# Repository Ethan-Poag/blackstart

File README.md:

# Project Blackstart

Open-source diesel generator controller: STM32 safety MCU, Raspberry Pi CM5 for UI and connectivity,
dual ADE9000 metering (600 V class), 12.1" display, 12 backlit keys, external LTE router over Ethernet.

Status: schematic complete (ERC 0/0), layout and enclosure in progress. Prototype for the maintainer's own use first.

**Board status on the m7 branches (m7-wip):** gate checkpoint only — 789 KiCad-unconnected items (was 791), NOT fab-ready, NOT safety-reviewed, NOT certified (600 V sign-off by a qualified safety engineer outstanding).
Not certified. Do not rely on it for safety until independently tested and reviewed.

See DESIGN_NOTES.md, docs/, and LICENSING.md.

## +12V rail notes (m7-wip, 2026-10-26)
- The 470 uF bulk caps C17/C18 (CP_Elec_10x10.5) on +12V sit about 160 mm (C17) and 174 mm (C18) from the LM5176 output FET Q6. The builder may want to move them near Q6. No ceramic bulk sits at Q6: the nearest +12V caps are C96 100 nF (11.6 mm) and C14 1 uF (24.6 mm).
- Trunk limit (inferred, IPC-2221 10 C, 1 oz outer assumed): narrowest trunk segment 1.5 mm, about 3.2 A supported against roughly 3.7 A estimated for U3+U15.
- Still unpowered on +12V: U24.3/C125 (backlight boost), U2.24 (LM5176 BIAS), C17, C18.

**Fusing:** Genctl has no on-board fuses (PTCs on small signal outputs only). The DI bias terminals (J21.6, J22.1) are for the digital-input contacts only: no external loads. The power-box K3 glow contactor (ALEV100-B/-C) has polarised load terminals: observe +A1 / -A2 (see docs/INSTALL_SAFETY.md). Do not plug or unplug the 600 V sense plugs J7/J8 (J28/J29) live: isolate the source or open the metering fuses first. Their field wire must be 600 V rated and stripped to 10 mm (Phoenix 1777859 plug), with no bare copper past the plug body; the LEFT_HV enclosure window needs its tool-removable-only hood (docs/INSTALL_SAFETY.md). All fuses and the power relays sit in the separate power box (docs/INSTALL_SAFETY.md, review/bom_final/BOM_powerbox.csv). Every output (FUEL, CRANK, GLOW, GCB/MCB,
AUX1–10, ESTOP_TRIP) has its own power box fuse position ahead of the relay or
solenoid, no larger than the output's maximum (5 A standard blade for FUEL/CRANK, which are limited to 2.8 A; 2 A small outputs; 2 A
ESTOP_TRIP relay drive) and sized down to the real load. The 30 A battery fuse does not protect individual
outputs. The J23.1/2 E-stop/fuel feed has its own 10 A ATO/ATC fuse (>=58 V DC, >=16 AWG wire) at power box position F2, after the 30 A battery fuse; that feed is not behind the over-voltage cut-off and must stay within the declared supply range (9–32 V continuous, up to 36 V for at most 60 s), never above about 40 V. Hardware maximum per main output: interposing relay coil class <= 2.8 A (software trip 3.0 A); E-stop trip coil < 1.70 A (U68, R407 47k; bench-measure); where a circuit has a lower limit or a 2 A fuse, that lower limit governs. Fit a flyback diode across every external coil. Declared limit: 12 V and 24 V DC battery systems only, with the battery permanently connected as the buffer. Supply 9–32 V DC continuous; up to 36 V for at most 60 s (24 V jump-start), during which the controller may switch itself off; above its over-voltage trip point, 36.35-40.06 V (component tolerance), it disconnects its internal supply, and after such an over-voltage trip the supply must fall below about 33 V before the controller restarts by itself. Short ISO 7637-type pulses are tolerated. Load dump of any kind, including a centrally suppressed 58 V load dump (ISO 16750-2 Test B), is not supported and has not been tested. The fuel solenoid must be energize-to-run. See docs/INSTALL_SAFETY.md. Not certified.

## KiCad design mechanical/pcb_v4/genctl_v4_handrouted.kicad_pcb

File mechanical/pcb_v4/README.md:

# Blackstart PCB v4: connectivity-driven placement and route pipeline

> **SUPERSEDED (N4, m7-sch 3c, 2026-10-28):** the schematic has no on-board fuse; battery net BAT_IN; installer fits an external fuse <=10 A standard (non-time-delay), >=58 V DC in the battery lead. Every F1 / VBAT_F / "fuse F1 10 A" / "10 A ATO" mention in this file describes the as-built .kicad_pcb (which still carries F1 clips and net VBAT_F until the board update) and is historical; the VBAT_F copper becomes BAT_IN when the board is updated. The 10 A copper figures remain a copper-capacity record only.

The board opens in KiCad 9/10 with `genctl_v4_routed.kicad_pcb` and `genctl_v4.kicad_pro`. The footprints are embedded and no plugins are needed.

## Pipeline (`pipeline.sh`)
Run it on the build box with KiCad 9 pcbnew python, Freerouting 2.5 and Java 25.

1. **place** (`place_v4.py`): hard constraints are locked first:
   - edges, keys, CM5 and display connectors
   - the 600 V box with its 13 mm barrier and slots, plus the isolators straddling it
   - posts, holes and the strap corridor

   After that come the **functional seeds**:
   - STM32, DSI83, bucks and ideal diode
   - ADE9000s, the CT stack and MOVs
   - J10/J11, which are rear-facing

   Every other IC goes to the weighted centroid of the parts it is already connected to (greedy, most-connected first). Each R/C/D/FB is assigned to its nearest IC on the same schematic sheet and lands right at the IC pin it shares, so decaps sit tight to their pins. Hot parts are confined to the HV box. Parts touching the line nets keep ≥1.4 mm between each other.
2. **critical** (`route_v4.py setup`):
   - **Netclasses:**
     - PWR 0.5 mm
     - DIFF100 0.11/0.15 (Ethernet, LVDS, DSI)
     - DIFF90 0.15/0.18 (USB)
     - HV_LINE 1.5 mm clearance (IPC-2221B B2, 600 V, inside the HV box)
   - **Plane zones:**
     - LV area: GND on In1/In4, +3V3_SAFE on In3
     - HV box: GND_AC on In1/In4, +3V3_AC on In3
   - **Plane fan-out:** a short stub and via from every SMD pad on a plane net, plus a via-in-pad grid on exposed pads.
3. **autoroute**: the remaining nets go to Freerouting via DSN/SES (`--router.fanout.enabled=false`).
4. **DRC**: `kicad-cli pcb drc`.
5. **render**: `render_v4.py`.

Rules: 0.10 mm track/space minimum, 0.20/0.40 mm vias. The impedance widths are **estimates** for JLC06161H-3313 and must be checked in JLC's impedance calculator.

**Fab note (m7-wip, 2026-10-25):** two DSI83_REFCLK vias, at (161.5, 126.7) and (162.0, 125.65) mm, are **0.15 mm drill / 0.30 mm pad**. Every other via is ≥0.2/0.35. I tried enlarging them to 0.2/0.35, but they do not fit: that breaks the DIFF100 clearance (0.125 vs 0.15 mm), the hole clearance (0.18 vs 0.20 mm) and the zone clearance (0.176 vs 0.20 mm). The board therefore needs JLC's "smaller via" option (0.15/0.25–0.3 mm class) at order time, which may add cost; check the JLC quote. The project's minimums are min through-hole 0.15 mm and min via 0.30 mm. The working and repo .kicad_pro files now agree on these values.

**Builder note (m7-wip, 2026-10-25): RV3 is NOT wired.** The GEN-side MOV RV3, at (25.26, 154.08) mm on B.Cu, is placed, but its pads RV3.1 (GEN_L3) and RV3.2 (GEN_N) have no copper. There is no legal 600 V path to its spot in the BUS area; it is an accepted placement exception (see HV_ACCEPTED_DEVIATIONS.md item 3). Do not assume GEN-side L3–N surge protection from RV3 on this board revision, and do not bodge-wire it without an HV spacing check.

## Known limit (m7-wip, 2026-10-26)
Superseded (2026-10-27, S3c/c6b): the board battery path is a 10 A path (F1 10 A) at 18 °F (10 °C) rise, INFERRED from the measured copper with 1 oz outer ASSUMED, not certified: VBAT_P Q2→Q3 F 8.76 / B 4.54 mm (11.5 / 7.2 A; F+B 18.7 A per the reviewer's tight-pad neck method, review/s3c6c/review.md, same on base and c6c; the earlier B 5.22 mm / 7.9 A / F+B 19.5 A was a method artefact, B alone < 10 A, so F+B sharing through the VBAT_P transfer vias is required: VBAT_P vias at the Q2 / Q3 ends, MEASURED with review/s3c6b/via_count.py (all 0.3/0.6 mm vias): primary method via-edge-to-pad-edge (any part of the via pad within r of any edge of the FET pads used: Q2 pads 1-3, Q3 pad 5) 25 / 25 within 5 mm and 40 / 35 within 8 mm; reviewer method via-centre-to-point (via centre within r of Q2 point (254.6, 151.0) / Q3 point (228.02, 140.07)) 17 / 14 within 5 mm and 34 / 25 within 8 mm; identical at 950b8a1 and S3c/c6c; 14 is met at both ends within 5 mm, exactly at the Q3 end), VBAT_DD Q1→Q2 F 7.54 / B 7.51 mm (10.3 / 10.3 A; F+B 20.7 A), VBAT_F F1→Q1 B 8.02 mm (10.8 A, reviewer tight-pad method; B only at Q1; F 8.95 mm before c6c, 1.92 mm after c6c, not counted) [M widths, tneck erosion on gate/s3c6b; amps I by IPC-2221 outer k 0.048 at 18 °F (10 °C) rise, 1 oz ASSUMED]. Caveat: the 10 A figure is the copper only. Continuous load is also limited by F1: a 10 A ATO carries at most about 8 A at 149 °F (65 °C) ambient (Littelfuse 287 ATOF derating, final_power_spec.md §1; datasheet pages UNVERIFIED). The battery wiring and the mating connector must be rated for the load as well. See docs/ROUTING_PLAN.md §8. Load shedding is fault-only, not a normal-operation behavior.

s3c6h (2026-10-27): C297 (220 nF / 100 V X7R since s3c6i; first 100 nF) on VBAT_F is the LM74800 CIN (TI SNOSD95C p23), at F.Cu (249.6, 137.0). The C1.1 VBAT_DD link moved from PWR to GND2, so the VBAT_F PWR pour is whole again: VBAT_F F1→Q1 PWR neck 8.952 mm [M], B 8.021 mm unchanged. See docs/ROUTING_PLAN.md §8.3. Not certified.

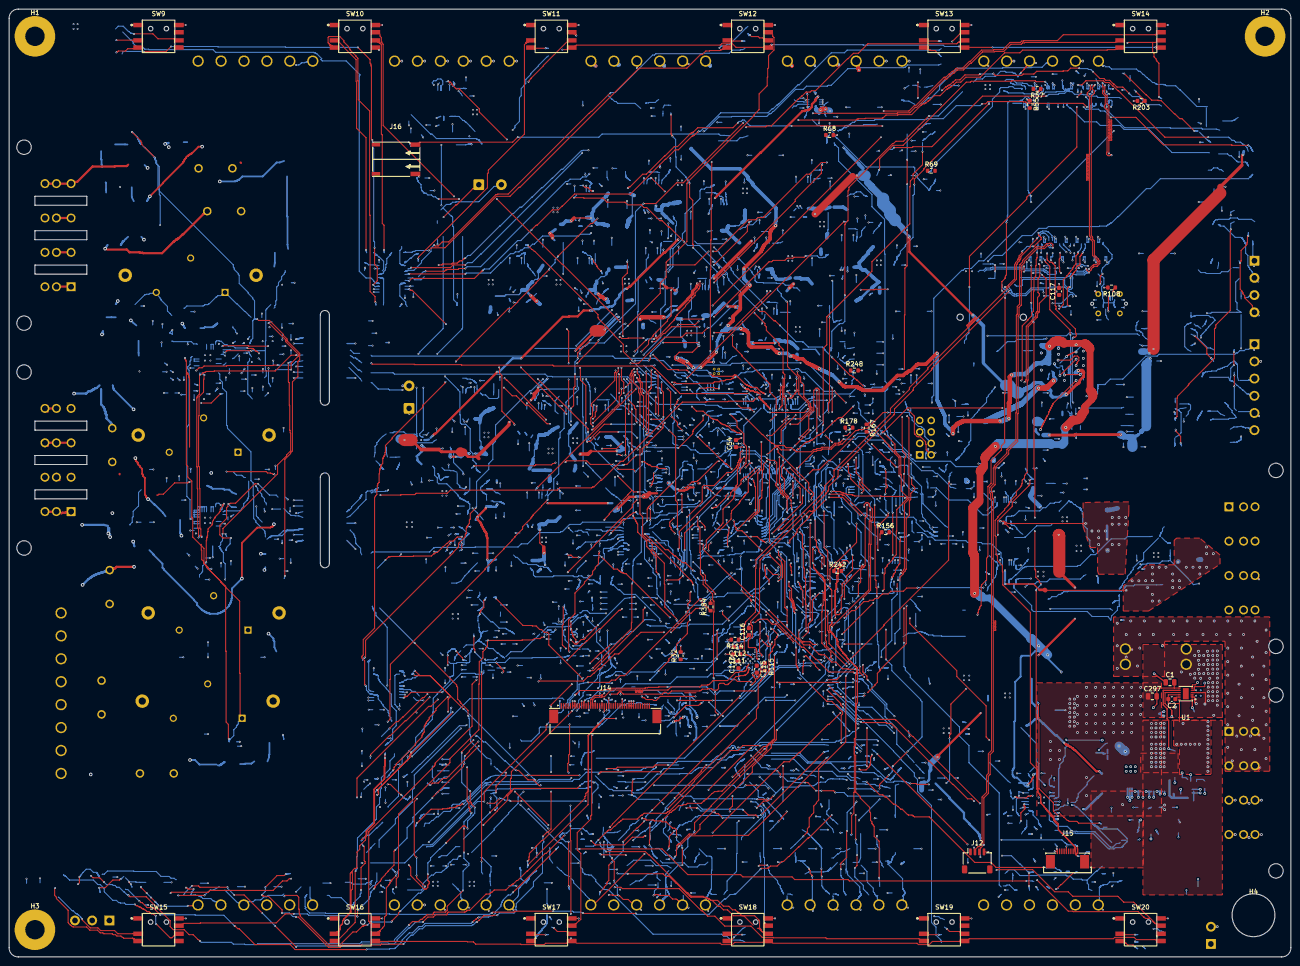
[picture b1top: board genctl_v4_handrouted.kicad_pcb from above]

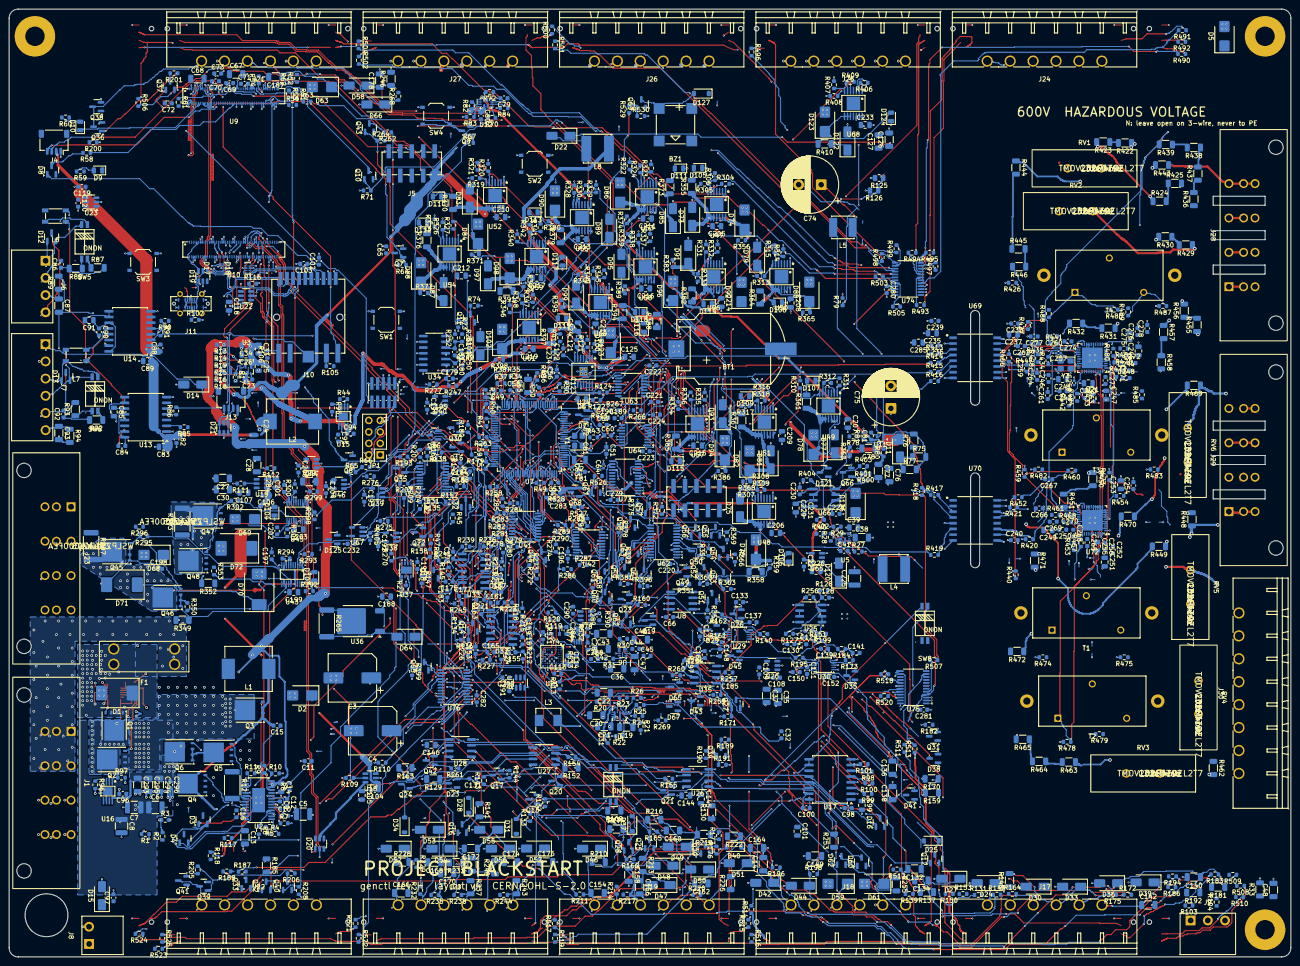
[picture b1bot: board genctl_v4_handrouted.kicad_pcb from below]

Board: 6 copper layers, 284.0 x 210.0 mm, 1184 parts (1138 on the bottom side), 819 nets.

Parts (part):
BT1: CR2032; BS-CR2032-8
BZ1: MLT-8530; MLT-8530_buzzer
C1, C39, C144, C145, C146, C188, C199, C203, C205, C206, C207, C208, C209, C210, C211, C212, C213, C214, C215, C216, C217, C218, C219, C233: 100n; C_0805_2012Metric
C2, C15, C16, C23, C31, C40, C49, C50, C51, C52, C53, C54, C57, C60, C65, C66, C69, C70, C71, C73, C79, C82, C84, C88, C90, C94, C96, C98, C100, C102, C110, C111, C112, C113, C128, C130, C131, C133, C135, C137, C139, C141, C143, C148, C150, C151, C152, C153, C155, C157, C159, C161, C163, C165, C167, C169, C171, C173, C175, C177, C179, C180, C182, C183, C184, C186, C189, C190, C191, C192, C193, C194, C195, C196, C200, C204, C220, C221, C223, C227, C228, C230, C231, C232, C234, C236, C238, C239, C240, C242, C244, C246, C248, C250, C252, C254, C256, C279, C280, C281, C282, C286, C288, C289, C290, C291, C292, C296: 100n; C_0603_1608Metric
C3, C4: 100u 50V; CP_Elec_10x10.5
C5, C6, C7, C8, C225: 10u; C_1210_3225Metric
C9, C12: 220p; C_0603_1608Metric
C10, C122: 47n; C_0603_1608Metric
C11, C259, C260, C261, C262, C263, C264, C265, C266, C267, C268, C269, C270, C271, C272, C273, C274, C275, C276, C277, C278: 33n; C_0603_1608Metric
C13, C55, C126, C127: 4.7u; C_1206_3216Metric
C14: 1u; C_0805_2012Metric
C19, C20, C21, C22, C27, C28, C29, C30, C35, C36, C37, C46, C47, C67, C68, C76, C77, C78, C293, C294, C295: 22u; C_1206_3216Metric
C24, C32, C287: 100p; C_0603_1608Metric
C25, C26, C33, C34, C83, C85, C89, C91, C99, C101, C105, C107, C114, C118, C124, C125, C235, C237, C247, C255, C284, C285: 10u; C_0805_2012Metric
C38: 2.2u; C_1206_3216Metric
C41, C44, C45, C56, C72, C80, C81, C104, C106, C108, C109, C115, C120, C121, C129, C283: 1u; C_0603_1608Metric
C42, C43: 47u; C_1206_3216Metric
C48, C87, C93: 4.7n; C_1206_3216Metric
C58, C59: 2.2u; C_0603_1608Metric
C61, C62, C63, C64: 18p; C_0402_1005Metric
C74, C75: 20F 3.0V; CP_Radial_D12.5mm_P5.00mm
C86, C92: 4.7n; C_0603_1608Metric
C95, C97, C103, C116, C181, C222, C224: 10n; C_0603_1608Metric
C117, C119, C185: 1n; C_0603_1608Metric
C123, C198, C202: 470n; C_0603_1608Metric
C132, C134, C136, C138, C140, C142, C147, C149, C154, C156, C158, C160, C162, C164, C166, C168, C170, C172, C174, C176, C178, C187: 100n; C_1206_3216Metric
C197, C201: 68n; C_0603_1608Metric
C226, C229: 2.2u; C_0805_2012Metric
C241, C243, C245, C249, C251, C253: 4.7u; C_0805_2012Metric
C257, C258: 22p; C_0402_1005Metric
C297: 220n; C_0805_2012Metric
D1: SMDJ36CA; D_SMC
D2, D68, D69, D74, D76, D78, D80, D82, D84, D86, D88, D90, D92, D94, D96, D98, D100, D102, D123, D126: SMBJ33CA; D_SMB
D3, D4: BAS70; SOT-23
D5: SMBJ5.0A; D_SMB
D6, D9, D103, D104, D105, D106, D107, D108, D109, D110, D111, D112, D113, D114, D115, D116, D117, D118, D119: green; LED_0805_2012Metric
D7, D8, D121: BAT54C; SOT-23
D10, D124: red; LED_0805_2012Metric
D11: SS34; D_SMA
D12, D13: NUP2105L; SOT-23
D14, D15, D64, D73, D75, D77, D79, D81, D83, D85, D87, D89, D91, D93, D95, D97, D99, D101, D120, D122: SS110; D_SMA
D16: SM712; SOT-23
D17, D18: RClamp0524P; RClamp0524P_SLP2510P8
D19, D20, D21: USBLC6-2SC6; SOT-23-6
D22: SS36; D_SMA
D23: LM4040A25; SOT-23
D24, D27, D30, D33, D36, D39, D42, D44, D46, D47, D48, D49, D50, D51, D52, D53, D54, D55, D56, D57, D58, D66: SMAJ36CA; D_SMA
D25, D28, D31, D34, D37, D40, D127: 1N4148W; D_SOD-123
D26, D29, D32, D35, D38, D41, D43, D45, D60, D62: BAV99; SOT-23
D59, D61: SMBJ58CA; D_SMB
D63: SMBJ36CA; D_SMB
D65, D67, D125: BAT54S; SOT-23
D70, D72: SK1010C; D_SMC
D71: SMDJ24A; D_SMC
F1: 10A ATO (3557-2 clips); Keystone_3557-2_ATO_clips
FB1: 600R@100MHz; L_0603_1608Metric
H1, H2, H3: M4 bezel boss; MountingHole_4.3mm_M4_Pad
H4: PE boss clearance D9.5 NPTH; MountingHole_4.3mm_M4
J1: PC 5/4-GF-7,62 (battery in); PhoenixContact_PC5_4-GF-7.62_1720819
J2: SWD; FTSH-105-01_SWD
J3: Header B (MCU spare); PZ254-2-05-S_2x05_SMD
J4: Fan header (SM04B); JST_SH_SM04B-SRSS-TB_1x04-1MP_P1.00mm_Horizontal
J5: Header A (CM5 I2C/SPI); PZ254-2-05-S_2x05_SMD
J6: CAN1 (PC 5/4); WJ15EDGRC-3.81-4P
J7: Expansion bus (PC 5/6); WJ15EDGRC-3.81-6P
J8: Router 12V (3.81/2); WJ15EDGRC-3.81-2P
J9: RS-485 (PC 5/3); WJ15EDGRC-3.81-3P
J10: HR963380AE; HR963380AE_RJ45
J11: USB-C service; USB_C_Receptacle_HRO_TYPE-C-31-D-06B_Vertical
J12: Internal USB0 touch (SM04B); JST_SH_SM04B-SRSS-TB_1x04-1MP_P1.00mm_Horizontal
J13: Internal USB1 spare (SM04B); JST_SH_SM04B-SRSS-TB_1x04-1MP_P1.00mm_Horizontal
J14: LVDS FPC 40p 0.5mm; FPC_40P_0.5_05A20L40P
J15: Touch FPC 10p 0.5mm; FPC_10P_0.5_05B20L10P
J16: Backlight (JST SM02B-BHSS); SM02B-BHSS-1-TB
J17: J1A analog in (PC 5/6); KF2EDGRM-5.08-6P
J18: J1B COM/MPU (PC 5/6); KF2EDGRM-5.08-6P
J19: J2A DI1-6; KF2EDGRM-5.08-6P
J20: J2B DI7-12; KF2EDGRM-5.08-6P
J21: J3A E-stop/D+/VBAT/bias; KF2EDGRM-5.08-6P
J22: J3B; KF2EDGRM-5.08-6P
J23: J4 E-stop/fuel/crank (PC 5/4-7.62); PhoenixContact_PC5_4-GF-7.62_1720819
J24: J5A outputs; KF2EDGRM-5.08-6P
J25: J5B returns; KF2EDGRM-5.08-6P
J26: J6A AUX1-6; KF2EDGRM-5.08-6P
J27: J6B AUX7-10 + returns; KF2EDGRM-5.08-6P
J28: J7 GEN voltage (L1 L2 L3 N); PhoenixContact_PC5_4-GF-7.62_1720819
J29: J8 BUS voltage (L1 L2 L3 N); PhoenixContact_PC5_4-GF-7.62_1720819
J30: J9 CT secondaries (5A); KF2EDGRM-5.08-8P
JP1: JP1 CM5->MCU SWD (opt); PinHeader_2x04_P2.54mm_Vertical
L1: 4.7u; L_SPM10065
L2: 3.3u; L_MWSA1004S
L3: 2.2u; L_MWSA0503S
L4: 33u; L_SWPA6045S
L5: 1u; L_FNR5020S
L6, L7: ACT45B-510-2P; ACT45B_CMC
L8: 10u; L_SWPA6045S
Q1, Q2, Q3, Q4, Q5, Q6, Q45, Q46, Q47, Q48: BSC070N10NS5; TDSON-8-1
Q7, Q8, Q9, Q10, Q11, Q14, Q18, Q22, Q26, Q30, Q34, Q37, Q40, Q43, Q44, Q49, Q50, Q51, Q52, Q53, Q54, Q55, Q56, Q57, Q58, Q59, Q60, Q61, Q62, Q63, Q64, Q65, Q66, Q67, Q69: MMBT3904; SOT-23
Q12, Q16, Q20, Q24, Q28, Q32: MMBT3906; SOT-23
Q13, Q17, Q21, Q25, Q29, Q33: BSS84; SOT-23
Q15, Q19, Q23, Q27, Q31, Q35, Q38, Q41: DMN6075S; SOT-23
Q36, Q39, Q42: SI2309CDS; SOT-23
Q68: AO3401A; SOT-23
R1: 210k; R_0603_1608Metric
R2: 49.9k; R_0603_1608Metric
R3: 9.76k; R_0603_1608Metric
R4, R11, R19, R26, R28, R32, R43, R64, R66, R68, R71, R73, R81, R97, R110, R112, R114, R115, R116, R121, R133, R134, R136, R138, R139, R144, R145, R147, R149, R150, R155, R156, R158, R160, R161, R166, R167, R169, R171, R172, R177, R178, R180, R182, R183, R188, R189, R191, R193, R194, R196, R198, R200, R201, R203, R204, R205, R206, R208, R209, R261, R262, R264, R266, R268, R273, R275, R276, R277, R278, R279, R280, R281, R282, R283, R284, R285, R286, R287, R288, R289, R290, R291, R292, R298, R350, R353, R356, R359, R362, R365, R368, R371, R374, R377, R380, R383, R386, R389, R392, R395, R398, R403, R405, R406, R411, R527, R530: 100k; R_0603_1608Metric
R5, R212, R215, R218, R221, R224, R227, R230, R233, R236, R239, R242, R245, R248, R250, R252: 33k; R_0603_1608Metric
R6: 93.1k; R_0603_1608Metric
R7: 27.4k; R_0603_1608Metric
R8: 4.7k; R_0603_1608Metric
R9: 140k; R_0603_1608Metric
R10, R17, R24, R31, R42, R44, R45, R48, R49, R63, R65, R67, R69, R70, R72, R74, R78, R79, R83, R101, R113, R117, R118, R124, R127, R128, R132, R135, R143, R146, R154, R157, R165, R168, R176, R179, R187, R190, R202, R207, R257, R263, R267, R269, R270, R271, R272, R274, R351, R354, R357, R360, R363, R366, R369, R372, R375, R378, R381, R384, R387, R390, R393, R396, R399, R401, R402, R412, R420, R421, R528: 10k; R_0603_1608Metric
R12: 8m; R_2512_6332Metric
R13, R20: 121k; R_0603_1608Metric
R14, R21: 16k; R_0603_1608Metric
R15, R22, R296, R302: 0R; R_0603_1608Metric
R16: 75k; R_0603_1608Metric
R18, R25: 20k; R_0603_1608Metric
R23: 45.3k; R_0603_1608Metric
R27, R109, R111, R304, R307, R310, R313, R316, R319, R322, R325, R328, R331, R334, R337, R340, R343, R346: 40.2k; R_0603_1608Metric
R29: 43.2k; R_0603_1608Metric
R30: 18.7k; R_0603_1608Metric
R33, R89, R94, R422, R423, R424, R425, R429, R430, R431, R432, R436, R437, R438, R439, R443, R444, R445, R446, R448, R449, R450, R451, R455, R456, R457, R458, R462, R463, R464, R465, R469, R470, R471, R472: 1M; R_1206_3216Metric
R34, R35, R36, R37, R38, R39, R40, R41, R50, R51, R52, R53, R54, R55, R56, R57, R58, R59, R60, R61, R62, R85, R86, R90, R91, R96, R98, R99, R100, R131, R142, R153, R164, R175, R186, R306, R309, R312, R315, R318, R321, R324, R327, R330, R333, R336, R339, R342, R345, R348, R409, R413, R414, R415, R416, R417, R418, R419, R426, R427, R428, R433, R434, R435, R440, R441, R442, R447, R452, R453, R454, R459, R460, R461, R466, R467, R468, R473, R476, R477, R480, R481, R484, R485, R488, R489, R526, R529: 1k; R_0603_1608Metric
R46, R47, R119, R120, R259, R260: 2.2k; R_0603_1608Metric
R75, R76, R77: 150R; R_1206_3216Metric
R80: 715k; R_0603_1608Metric
R82: 33.2k; R_0603_1608Metric
R84: 29.4k; R_0603_1608Metric
R87, R88, R92, R93: 62R; R_1206_3216Metric
R95: 1.33k; R_0603_1608Metric
R102: 120R; R_1206_3216Metric
R103, R104: 680R; R_0603_1608Metric
R105, R106, R492, R495, R498, R501, R504, R507, R510, R513, R516, R519, R522, R525: 330R; R_0603_1608Metric
R107, R108: 5.1k; R_0603_1608Metric
R122: 180k; R_0603_1608Metric
R123: 232k; R_0603_1608Metric
R125, R126: 1.1R; R_0805_2012Metric
R129, R253, R255, R349, R352, R355, R358, R361, R364, R367, R370, R373, R376, R379, R382, R385, R388, R391, R394, R397, R410: 10k; R_1206_3216Metric
R130, R141, R152, R163, R174, R185: 2.49k; R_1206_3216Metric
R137, R148, R159, R170, R181, R192: 100R; R_1206_3216Metric
R140, R151, R162, R173, R184, R195, R197, R199: 18k; R_0603_1608Metric
R210, R213, R216, R219, R222, R225, R228, R231, R234, R237, R240, R243, R246: 4.7k; R_1206_3216Metric
R211, R214, R217, R220, R223, R226, R229, R232, R235, R238, R241, R244, R247, R249, R251: 68k; R_0603_1608Metric
R254, R256, R258: 1M; R_0603_1608Metric
R265: 10R; R_2512_6332Metric
R293, R299: 27k; R_0603_1608Metric
R294, R300: 35.7k; R_0603_1608Metric
R295, R301: 10R; R_0603_1608Metric
R297, R303: 1m; R_2512_6332Metric
R305, R308, R311, R314, R317, R320, R323, R326, R329, R332, R335, R338, R341, R344, R347, R408: 1.1k; R_0603_1608Metric
R400, R407, R533: 47k; R_0603_1608Metric
R404, R532: 200k; R_0603_1608Metric
R474, R475, R478, R479, R482, R483, R486, R487: 24.9R; R_0603_1608Metric
R490, R491, R493, R494, R496, R497, R499, R500, R502, R503, R505, R506, R508, R509, R511, R512, R514, R515, R517, R518, R520, R521, R523, R524: 470R; R_0603_1608Metric
R531: 22R; R_0603_1608Metric
RV1, RV2, RV3, RV4, RV5, RV6: TMOV20RP460E; TMOV20RP_P7.5mm_inline
SW1: RESET; SW_Push_1P1T_XKB_TS-1187A
SW2: BOOT0; SW_Push_1P1T_XKB_TS-1187A
SW3: nRPIBOOT; SW_Push_1P1T_XKB_TS-1187A
SW4: CM5 PWR; SW_Push_1P1T_XKB_TS-1187A
SW5, SW6: TERM; DSHP02TSGER_DIP2
SW7: TERM/BIAS; DSHP02TSGER_DIP2
SW8: BIAS; DSHP02TSGER_DIP2
SW9: BTN1; CTS_228E_RGB
SW10: BTN2; CTS_228E_RGB
SW11: BTN3; CTS_228E_RGB
SW12: BTN4; CTS_228E_RGB
SW13: BTN5; CTS_228E_RGB
SW14: BTN6; CTS_228E_RGB
SW15: BTN7; CTS_228E_RGB
SW16: BTN8; CTS_228E_RGB
SW17: BTN9; CTS_228E_RGB
SW18: BTN10; CTS_228E_RGB
SW19: BTN11; CTS_228E_RGB
SW20: BTN12; CTS_228E_RGB
T1, T2, T3, T4: AC1005; AC1005_CT
U1: LM74800QDRRRQ1; LM74800_WSON-12_3x3
U2: LM5176PWPR; HTSSOP-28-1EP_4.4x9.7mm_P0.65mm_EP2.85x5.4mm
U3, U4: TPS56637RPAR; TPS56637_VQFN-HR-10_RPA
U5: LMR36506RRPER; LMR36506_VQFN-HR-9_RPE
U6: TPS2116DRLR; SOT-583-8
U7: STM32H743VIT6; LQFP-100_14x14mm_P0.5mm
U8: FM24CL64B; SOIC-8_3.9x4.9mm_P1.27mm
U9: CM5 (conn A); DF40C-100DS-0.4V
U10: CM5 (conn B); DF40C-100DS-0.4V_B
U11: TPS61023DRLR; SOT-563
U12: TPS2121RUXR; TPS2121_VQFN-HR-12_RUX
U13, U14: CA-IS3062W; SOIC-16W_7.5x10.3mm_P1.27mm
U15, U16: TPS1H200AQDGNRQ1; TPS1H200_MSOP-8-EP_DGN
U17: CA-IS2092W; SOIC-16W_7.5x10.3mm_P1.27mm
U18, U19: TPS2553DBVR; SOT-23-6
U20: TLV75518PDBVR; SOT-23-5
U21: SN65DSI83ZXHR; SN65DSI83_nFBGA-64_ZXH
U22, U23: TPS22918DBVR; SOT-23-6
U24: TPS61500PWPR; TPS61500_HTSSOP-14_PWP
U25: TLV9062; SOIC-8_3.9x4.9mm_P1.27mm
U26, U27, U28: LM2904; SOIC-8_3.9x4.9mm_P1.27mm
U29: ADS1115 @0x48; TSSOP-10_3x3mm_P0.5mm
U30: ADS1115 @0x49; TSSOP-10_3x3mm_P0.5mm
U31: TCA9555PWR @0x22; TSSOP-24_4.4x7.8mm_P0.65mm
U32, U33, U34: 74HC14; SOIC-14_3.9x8.7mm_P1.27mm
U35: LM393; SOIC-8_3.9x4.9mm_P1.27mm
U36: LM317M; TO-252-2
U37: TPS3431SQDRBRQ1; TPS3431_VSON-8_DRB
U38, U39, U40, U67: 74LVC1G08; SOT-23-5
U41, U42: SN74LVC541APWR; TSSOP-20_4.4x6.5mm_P0.65mm
U43, U45: TPS48100QDGXRQ1; TPS48100_VSSOP-19_DGX
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
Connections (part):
+1V8_DSI: C109.1, C110.1, C111.1, C112.1, C113.1, C114.1, C286.1, C288.1, C290.1, C291.1, R119.2, R120.2, U20.5, U21.A9, U21.B8, U21.D6, U21.E5, U21.E6, U21.F6, U21.J2, U77.2, U78.6, U79.1, U79.5, Y4.1, Y4.4
+3V3: BZ1.1, C32.1, C35.1, C36.1, C37.1, C44.1, C98.1, C99.1, C108.1, C235.1, C236.1, C239.1, C285.1, D127.1, L3.2, R23.1, R30.1, U6.3, U6.5, U17.1, U20.1, U20.3, U22.1, U23.1, U69.1, U70.1, U70.7
+3V3_AC: C237.1, C238.1, C240.1, C247.1, C248.1, C255.1, C256.1, R420.2, R421.2, U69.16, U70.10, U70.16, U71.1, U71.27, U72.1, U72.27
+3V3_BK: C42.1, C43.1, C45.1, L4.2, R28.1, U6.6
+3V3_PANEL: C118.1, J14.2, J14.3, J14.4, U22.5, U22.6
+3V3_SAFE: C46.1, C47.1, C49.1, C50.1, C51.1, C52.1, C53.1, C54.1, C55.1, C66.1, C130.1, C151.1, C152.1, C153.1, C182.1, C183.1, C184.1, C186.1, C191.1, C192.1, C193.1, C194.1, C195.1, C196.1, C200.1, C204.1, C220.1, C221.1, C223.1, C232.1, C279.1, C280.1, C281.1, C282.1, D7.1, D26.2, D29.2, D32.2, D35.2, D38.2, D41.2, D43.2, D45.2, D60.2, D62.2, D65.2, D67.2, D125.2, FB1.1, J2.1, J3.1, R11.2, R19.2, R26.2, R32.2, R44.2, R45.2, R46.2, R47.2, R48.2, R74.2, R97.2, R110.2, R112.2, R127.1, R259.2, R260.2, R270.2, R271.2, R274.2, SW2.2, U6.2, U6.7, U7.11, U7.20, U7.27, U7.50, U7.75, U7.100, U8.8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
+3V3_TOUCH: C120.1, J15.6, R117.2, R118.2, U23.5, U23.6
+5V: C24.1, C27.1, C28.1, C29.1, C30.1, C80.1, C82.1, C83.1, C88.1, C89.1, C104.1, C106.1, C284.1, D5.1, D11.2, J3.8, J4.2, J5.2, L2.2, Q68.2, R16.1, R82.1, R528.1, U12.7, U13.1, U14.1, U18.1, U19.1
+5V_CM5: C67.1, C68.1, C69.1, C70.1, U9.77, U9.79, U9.81, U9.83, U9.85, U9.87, U12.1, U12.8
+5V_HU: C77.1, C78.1, C81.1, R80.1, U11.6, U12.2
+5V_TRIP: C226.1, C227.1, C231.1, R402.1, R404.1, U65.5, U66.8
+12V: C14.1, C19.1, C20.1, C21.1, C22.1, C25.1, C26.1, C33.1, C34.1, C94.1, C96.1, C124.1, C125.1, C293.1, C294.1, C295.1, C296.1, L8.1, Q6.5, R9.1, R13.1, R20.1, U2.12, U2.13, U2.14, U3.8, U4.8, U15.8, U16.8, U24.3
/AC metering: 2x ADE9000 (gen + bus), isolated/AC_CS1_N: U69.12, U71.40
/AC metering: 2x ADE9000 (gen + bus), isolated/AC_CS2_N: U70.14, U72.40
/AC metering: 2x ADE9000 (gen + bus), isolated/AC_IRQ_N: R420.1, U70.11, U71.31
/AC metering: 2x ADE9000 (gen + bus), isolated/AC_MISO: U69.11, U71.38, U72.38
/AC metering: 2x ADE9000 (gen + bus), isolated/AC_MOSI: U69.13, U71.39, U72.39
/AC metering: 2x ADE9000 (gen + bus), isolated/AC_RST_N: R421.1, U70.13, U71.6, U72.6
/AC metering: 2x ADE9000 (gen + bus), isolated/AC_SCK: U69.14, U71.37, U72.37
/AC metering: 2x ADE9000 (gen + bus), isolated/ADE_IRQ_N_I: R419.2, U70.6
/AC metering: 2x ADE9000 (gen + bus), isolated/ADE_MISO_I: R416.2, U69.6
/AC metering: 2x ADE9000 (gen + bus), isolated/ADE_MOSI_I: R414.2, U69.4
/AC metering: 2x ADE9000 (gen + bus), isolated/ADE_SCK_I: R413.2, U69.3
/AC metering: 2x ADE9000 (gen + bus), isolated/ADE_XI: C257.1, U71.29, Y3.1
/AC metering: 2x ADE9000 (gen + bus), isolated/ADE_XO: C258.1, U71.30, U72.29, Y3.3
/AC metering: 2x ADE9000 (gen + bus), isolated/BUS_L1: J29.1, R448.1, RV4.1
/AC metering: 2x ADE9000 (gen + bus), isolated/BUS_L2: J29.2, R455.1, RV5.1
/AC metering: 2x ADE9000 (gen + bus), isolated/BUS_L3: J29.3, R462.1, RV6.1
/AC metering: 2x ADE9000 (gen + bus), isolated/BUS_N: J29.4, R469.1, RV4.2, RV5.2, RV6.2
/AC metering: 2x ADE9000 (gen + bus), isolated/BUS_VA_N: C266.1, R454.2, U72.19
/AC metering: 2x ADE9000 (gen + bus), isolated/BUS_VB_N: C268.1, R461.2, U72.21
/AC metering: 2x ADE9000 (gen + bus), isolated/BUS_VB_P: C267.1, R460.2, U72.22
/AC metering: 2x ADE9000 (gen + bus), isolated/BUS_VB_TAP: R458.2, R459.1, R460.1
/AC metering: 2x ADE9000 (gen + bus), isolated/BUS_VC_N: C270.1, R468.2, U72.23
/AC metering: 2x ADE9000 (gen + bus), isolated/BUS_VC_P: C269.1, R467.2, U72.24
/AC metering: 2x ADE9000 (gen + bus), isolated/BUS_VC_TAP: R465.2, R466.1, R467.1
/AC metering: 2x ADE9000 (gen + bus), isolated/BUS_VN_TAP: R454.1, R461.1, R468.1, R472.2, R473.1
/AC metering: 2x ADE9000 (gen + bus), isolated/CT1_S1: J30.1, T1.4
/AC metering: 2x ADE9000 (gen + bus), isolated/CT1_S2: J30.2, T1.5
/AC metering: 2x ADE9000 (gen + bus), isolated/CT2_S1: J30.3, T2.4
/AC metering: 2x ADE9000 (gen + bus), isolated/CT2_S2: J30.4, T2.5
/AC metering: 2x ADE9000 (gen + bus), isolated/CT3_S1: J30.5, T3.4
/AC metering: 2x ADE9000 (gen + bus), isolated/CT3_S2: J30.6, T3.5
/AC metering: 2x ADE9000 (gen + bus), isolated/CT4_S1: J30.7, T4.4
/AC metering: 2x ADE9000 (gen + bus), isolated/CT4_S2: J30.8, T4.5
/AC metering: 2x ADE9000 (gen + bus), isolated/GEN_CTA_1: R474.1, R476.1, T1.1
/AC metering: 2x ADE9000 (gen + bus), isolated/GEN_CTA_2: R475.1, R477.1, T1.2
/AC metering: 2x ADE9000 (gen + bus), isolated/GEN_CTB_1: R478.1, R480.1, T2.1
/AC metering: 2x ADE9000 (gen + bus), isolated/GEN_CTB_2: R479.1, R481.1, T2.2
/AC metering: 2x ADE9000 (gen + bus), isolated/GEN_CTC_1: R482.1, R484.1, T3.1
/AC metering: 2x ADE9000 (gen + bus), isolated/GEN_CTC_2: R483.1, R485.1, T3.2
/AC metering: 2x ADE9000 (gen + bus), isolated/GEN_CTN_1: R486.1, R488.1, T4.1
/AC metering: 2x ADE9000 (gen + bus), isolated/GEN_CTN_2: R487.1, R489.1, T4.2
/AC metering: 2x ADE9000 (gen + bus), isolated/GEN_IA_N: C272.1, R477.2, U71.8
/AC metering: 2x ADE9000 (gen + bus), isolated/GEN_IA_P: C271.1, R476.2, U71.7
/AC metering: 2x ADE9000 (gen + bus), isolated/GEN_IB_N: C274.1, R481.2, U71.10
/AC metering: 2x ADE9000 (gen + bus), isolated/GEN_IB_P: C273.1, R480.2, U71.9
/AC metering: 2x ADE9000 (gen + bus), isolated/GEN_IC_N: C276.1, R485.2, U71.12
/AC metering: 2x ADE9000 (gen + bus), isolated/GEN_IC_P: C275.1, R484.2, U71.11
/AC metering: 2x ADE9000 (gen + bus), isolated/GEN_IN_N: C278.1, R489.2, U71.14
/AC metering: 2x ADE9000 (gen + bus), isolated/GEN_IN_P: C277.1, R488.2, U71.13
/AC metering: 2x ADE9000 (gen + bus), isolated/GEN_L1: J28.1, R422.1, RV1.1
/AC metering: 2x ADE9000 (gen + bus), isolated/GEN_L2: J28.2, R429.1, RV2.1
/AC metering: 2x ADE9000 (gen + bus), isolated/GEN_L3: J28.3, R436.1, RV3.1
/AC metering: 2x ADE9000 (gen + bus), isolated/GEN_N: J28.4, R443.1, RV1.2, RV2.2, RV3.2
/AC metering: 2x ADE9000 (gen + bus), isolated/GEN_VA_N: C260.1, R428.2, U71.19
/AC metering: 2x ADE9000 (gen + bus), isolated/GEN_VA_P: C259.1, R427.2, U71.20
/AC metering: 2x ADE9000 (gen + bus), isolated/GEN_VB_N: C262.1, R435.2, U71.21
/AC metering: 2x ADE9000 (gen + bus), isolated/GEN_VB_P: C261.1, R434.2, U71.22
/AC metering: 2x ADE9000 (gen + bus), isolated/GEN_VC_N: C264.1, R442.2, U71.23
/AC metering: 2x ADE9000 (gen + bus), isolated/GEN_VC_P: C263.1, R441.2, U71.24
/AC metering: 2x ADE9000 (gen + bus), isolated/GEN_VN_TAP: R428.1, R435.1, R442.1, R446.2, R447.1
/AC metering: 2x ADE9000 (gen + bus), isolated/REF_BUS: C253.1, C254.1, U72.16
/AC metering: 2x ADE9000 (gen + bus), isolated/REF_GEN: C245.1, C246.1, U71.16
/Comms: CAN x2, RS-485, Ethernet, USB hub/ports, router 12V/CAN1_H: L6.1, U13.13
/Comms: CAN x2, RS-485, Ethernet, USB hub/ports, router 12V/CAN1_HB: D12.1, J6.1, L6.4, SW5.1
/Comms: CAN x2, RS-485, Ethernet, USB hub/ports, router 12V/CAN1_L: L6.2, U13.12
/Comms: CAN x2, RS-485, Ethernet, USB hub/ports, router 12V/CAN1_LB: D12.2, J6.2, L6.3, SW5.2
/Comms: CAN x2, RS-485, Ethernet, USB hub/ports, router 12V/CAN1_RX_T: R86.1, U13.5
/Comms: CAN x2, RS-485, Ethernet, USB hub/ports, router 12V/CAN1_SCR: C87.1, J6.3, R89.1
/Comms: CAN x2, RS-485, Ethernet, USB hub/ports, router 12V/CAN1_TH: R87.1, SW5.4
/Comms: CAN x2, RS-485, Ethernet, USB hub/ports, router 12V/CAN1_TL: R88.1, SW5.3
/Comms: CAN x2, RS-485, Ethernet, USB hub/ports, router 12V/CAN2_H: L7.1, U14.13
/Comms: CAN x2, RS-485, Ethernet, USB hub/ports, router 12V/CAN2_HB: D13.1, J7.3, L7.4, SW6.1
/Comms: CAN x2, RS-485, Ethernet, USB hub/ports, router 12V/CAN2_L: L7.2, U14.12
/Comms: CAN x2, RS-485, Ethernet, USB hub/ports, router 12V/CAN2_LB: D13.2, J7.4, L7.3, SW6.2
/Comms: CAN x2, RS-485, Ethernet, USB hub/ports, router 12V/CAN2_RX_T: R91.1, U14.5
/Comms: CAN x2, RS-485, Ethernet, USB hub/ports, router 12V/CAN2_TH: R92.1, SW6.4
/Comms: CAN x2, RS-485, Ethernet, USB hub/ports, router 12V/CAN2_TL: R93.1, SW6.3
/Comms: CAN x2, RS-485, Ethernet, USB hub/ports, router 12V/EXP12_CL: R95.1, U15.4
/Comms: CAN x2, RS-485, Ethernet, USB hub/ports, router 12V/EXP_12V: C95.1, D14.1, J7.1, U15.7
/Comms: CAN x2, RS-485, Ethernet, USB hub/ports, router 12V/RS485_A: D16.1, J9.1, R103.2, SW7.1, U17.12
/Comms: CAN x2, RS-485, Ethernet, USB hub/ports, router 12V/RS485_B: D16.2, J9.2, R104.2, SW7.2, U17.13
/Comms: CAN x2, RS-485, Ethernet, USB hub/ports, router 12V/RS485_BIASN: R104.1, SW8.3
/Comms: CAN x2, RS-485, Ethernet, USB hub/ports, router 12V/RS485_BIASP: R103.1, SW8.4
/Comms: CAN x2, RS-485, Ethernet, USB hub/ports, router 12V/RS485_TA: R102.1, SW7.4
/Comms: CAN x2, RS-485, Ethernet, USB hub/ports, router 12V/RS485_TB: R102.2, SW7.3
/Comms: CAN x2, RS-485, Ethernet, USB hub/ports, router 12V/USB0_5V: C105.1, D20.5, J12.1, U18.6
/Comms: CAN x2, RS-485, Ethernet, USB hub/ports, router 12V/USB1_5V: C107.1, D21.5, J13.1, U19.6
/Comms: CAN x2, RS-485, Ethernet, USB hub/ports, router 12V/USBC_CC2: J11.B5, R108.1
/Comms: CAN x2, RS-485, Ethernet, USB hub/ports, router 12V/USBC_VBUS: D19.5, J11.A4, J11.A9, J11.B4, J11.B9
/Display: DSI->LVDS bridge, panel power, backlight, touch/BL_COMP: C123.1, U24.8
/Display: DSI->LVDS bridge, panel power, backlight, touch/BL_DIMC: C121.1, U24.6
/Display: DSI->LVDS bridge, panel power, backlight, touch/BL_FREQ: R122.1, U24.10
/Display: DSI->LVDS bridge, panel power, backlight, touch/BL_SS: C122.1, U24.5
/Display: DSI->LVDS bridge, panel power, backlight, touch/DISP_SCL_1V8: R119.1, U21.H1, U77.3
/Display: DSI->LVDS bridge, panel power, backlight, touch/DISP_SDA_1V8: R120.1, U21.J1, U77.4
/Display: DSI->LVDS bridge, panel power, backlight, touch/DSI83_EN_1V8: C116.1, R533.1, U21.B1, U78.4
/Display: DSI->LVDS bridge, panel power, backlight, touch/DSI83_IRQ_1V8: R115.1, U21.J9, U79.3
/Display: DSI->LVDS bridge, panel power, backlight, touch/DSI83_REFCLK: R113.1, R531.2, U21.H2
/Display: DSI->LVDS bridge, panel power, backlight, touch/DSI83_REFCLK_OSC: R531.1, Y4.3
/Display: DSI->LVDS bridge, panel power, backlight, touch/DSI83_VCORE: C115.1, U21.J8
/Display: DSI->LVDS bridge, panel power, backlight, touch/LVDS0_N: J14.8, U21.C9
/Display: DSI->LVDS bridge, panel power, backlight, touch/LVDS0_P: J14.9, U21.C8
/Display: DSI->LVDS bridge, panel power, backlight, touch/LVDS1_N: J14.11, U21.D9
/Display: DSI->LVDS bridge, panel power, backlight, touch/LVDS1_P: J14.12, U21.D8
/Display: DSI->LVDS bridge, panel power, backlight, touch/LVDS2_N: J14.14, U21.E9
/Display: DSI->LVDS bridge, panel power, backlight, touch/LVDS2_P: J14.15, U21.E8
/Display: DSI->LVDS bridge, panel power, backlight, touch/LVDS3_N: J14.20, U21.G9
/Display: DSI->LVDS bridge, panel power, backlight, touch/LVDS3_P: J14.21, U21.G8
/Display: DSI->LVDS bridge, panel power, backlight, touch/LVDSC_N: J14.17, U21.F9
/Display: DSI->LVDS bridge, panel power, backlight, touch/LVDSC_P: J14.18, U21.F8
/Display: DSI->LVDS bridge, panel power, backlight, touch/VLED: C126.1, C127.1, D22.1, J16.1, R123.1
/E-stop trip and sense/ESTOP_TRIP_EN: D121.3, R406.1, U68.2
/E-stop trip and sense/ESTOP_TRIP_ILIM: R407.1, U68.7
/E-stop trip and sense/ESTOP_TRIP_LED: D124.2, R410.2
/E-stop trip and sense/MCU_TRIP_G: D121.2, U67.4
/E-stop trip and sense/TRIP_555_Q: D121.1, U66.3
/E-stop trip and sense/TRIP_CV: C230.1, U66.5
/E-stop trip and sense/TRIP_QB: Q66.1, R400.2, R401.1
/E-stop trip and sense/TRIP_TRIG: C228.1, R403.2, U66.2
/Front panel: backlit buttons, buzzer/BL1_B: R492.2, U74.6
/Front panel: backlit buttons, buzzer/BL1_G: R491.2, U74.5
/Front panel: backlit buttons, buzzer/BL1_R: R490.2, U74.4
/Front panel: backlit buttons, buzzer/BL2_B: R495.2, U74.9
/Front panel: backlit buttons, buzzer/BL2_G: R494.2, U74.8
/Front panel: backlit buttons, buzzer/BL2_R: R493.2, U74.7
/Front panel: backlit buttons, buzzer/BL3_B: R498.2, U74.13
/Front panel: backlit buttons, buzzer/BL3_G: R497.2, U74.11
/Front panel: backlit buttons, buzzer/BL3_R: R496.2, U74.10
/Front panel: backlit buttons, buzzer/BL4_B: R501.2, U74.16
/Front panel: backlit buttons, buzzer/BL4_G: R500.2, U74.15
/Front panel: backlit buttons, buzzer/BL4_R: R499.2, U74.14
/Front panel: backlit buttons, buzzer/BL5_B: R504.2, U74.19
/Front panel: backlit buttons, buzzer/BL5_G: R503.2, U74.18
/Front panel: backlit buttons, buzzer/BL5_R: R502.2, U74.17
/Front panel: backlit buttons, buzzer/BL6_B: R507.2, U75.5
/Front panel: backlit buttons, buzzer/BL6_G: R506.2, U75.4
/Front panel: backlit buttons, buzzer/BL6_R: R505.2, U74.20
/Front panel: backlit buttons, buzzer/BL7_B: R510.2, U75.8
/Front panel: backlit buttons, buzzer/BL7_G: R509.2, U75.7
/Front panel: backlit buttons, buzzer/BL7_R: R508.2, U75.6
/Front panel: backlit buttons, buzzer/BL8_B: R513.2, U75.11
/Front panel: backlit buttons, buzzer/BL8_G: R512.2, U75.10
/Front panel: backlit buttons, buzzer/BL8_R: R511.2, U75.9
/Front panel: backlit buttons, buzzer/BL9_B: R516.2, U75.15
/Front panel: backlit buttons, buzzer/BL9_G: R515.2, U75.14
/Front panel: backlit buttons, buzzer/BL9_R: R514.2, U75.13
/Front panel: backlit buttons, buzzer/BL10_B: R519.2, U75.18
/Front panel: backlit buttons, buzzer/BL10_G: R518.2, U75.17
/Front panel: backlit buttons, buzzer/BL10_R: R517.2, U75.16
/Front panel: backlit buttons, buzzer/BL11_B: R522.2, U76.4
/Front panel: backlit buttons, buzzer/BL11_G: R521.2, U75.20
/Front panel: backlit buttons, buzzer/BL11_R: R520.2, U75.19
/Front panel: backlit buttons, buzzer/BL12_B: R525.2, U76.7
/Front panel: backlit buttons, buzzer/BL12_G: R524.2, U76.6
/Front panel: backlit buttons, buzzer/BL12_R: R523.2, U76.5
/Front panel: backlit buttons, buzzer/BL_PG: Q67.3, Q68.1, R528.2
/Front panel: backlit buttons, buzzer/BTN1: SW9.3, U73.4
/Front panel: backlit buttons, buzzer/BTN1_BK: R492.1, SW9.7
/Front panel: backlit buttons, buzzer/BTN2: SW10.3, U73.5
/Front panel: backlit buttons, buzzer/BTN2_BK: R495.1, SW10.7
/Front panel: backlit buttons, buzzer/BTN3: SW11.3, U73.6
/Front panel: backlit buttons, buzzer/BTN3_BK: R498.1, SW11.7
/Front panel: backlit buttons, buzzer/BTN4: SW12.3, U73.7
/Front panel: backlit buttons, buzzer/BTN4_BK: R501.1, SW12.7
/Front panel: backlit buttons, buzzer/BTN5: SW13.3, U73.8
/Front panel: backlit buttons, buzzer/BTN5_BK: R504.1, SW13.7
/Front panel: backlit buttons, buzzer/BTN6: SW14.3, U73.9
/Front panel: backlit buttons, buzzer/BTN6_BK: R507.1, SW14.7
/Front panel: backlit buttons, buzzer/BTN7: SW15.3, U73.10
/Front panel: backlit buttons, buzzer/BTN7_BK: R510.1, SW15.7
/Front panel: backlit buttons, buzzer/BTN8: SW16.3, U73.11
/Front panel: backlit buttons, buzzer/BTN8_BK: R513.1, SW16.7
/Front panel: backlit buttons, buzzer/BTN9: SW17.3, U73.13
/Front panel: backlit buttons, buzzer/BTN9_BK: R516.1, SW17.7
/Front panel: backlit buttons, buzzer/BTN10: SW18.3, U73.14
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
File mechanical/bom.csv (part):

"Reference","Value","Footprint","QUANTITY"
"BT1","CR2032","genctl:BS-CR2032-8","1"
"BZ1","MLT-8530","genctl:MLT-8530_buzzer","1"
"C1,C39,C144-C146,C188,C199,C203,C205-C219,C233","100n","Capacitor_SMD:C_0805_2012Metric","24"
"C297","220n","Capacitor_SMD:C_0805_2012Metric","1"
"C2,C15,C16,C23,C31,C40,C49-C54,C57,C60,C65,C66,C69-C71,C73,C79,C82,C84,C88,C90,C94,C96,C98,C100,C102,C110-C113,C128,C130,C131,C133,C135,C137,C139,C141,C143,C148,C150-C153,C155,C157,C159,C161,C163,C165,C167,C169,C171,C173,C175,C177,C179,C180,C182-C184,C186,C189-C196,C200,C204,C220,C221,C223,C227,C228,C230-C232,C234,C236,C238-C240,C242,C244,C246,C248,C250,C252,C254,C256,C279-C282,C286,C288-C292,C296","100n","Capacitor_SMD:C_0603_1608Metric","108"
"C3,C4","100u 50V","Capacitor_SMD:CP_Elec_10x10.5","2"
"C5-C8,C225","10u","Capacitor_SMD:C_1210_3225Metric","5"
"C9,C12","220p","Capacitor_SMD:C_0603_1608Metric","2"
"C10,C122","47n","Capacitor_SMD:C_0603_1608Metric","2"
"C11,C259-C278","33n","Capacitor_SMD:C_0603_1608Metric","21"
"C13,C55,C126,C127","4.7u","Capacitor_SMD:C_1206_3216Metric","4"
"C14","1u","Capacitor_SMD:C_0805_2012Metric","1"
"C19-C22,C27-C30,C35-C37,C46,C47,C67,C68,C76-C78,C293-C295","22u","Capacitor_SMD:C_1206_3216Metric","21"
"C24,C32,C287","100p","Capacitor_SMD:C_0603_1608Metric","3"
"C25,C26,C33,C34,C83,C85,C89,C91,C99,C101,C105,C107,C114,C118,C124,C125,C235,C237,C247,C255,C284,C285","10u","Capacitor_SMD:C_0805_2012Metric","22"
"C38","2.2u","Capacitor_SMD:C_1206_3216Metric","1"
"C41,C44,C45,C56,C72,C80,C81,C104,C106,C108,C109,C115,C120,C121,C129,C283","1u","Capacitor_SMD:C_0603_1608Metric","16"
"C42,C43","47u","Capacitor_SMD:C_1206_3216Metric","2"
"C48,C87,C93","4.7n","Capacitor_SMD:C_1206_3216Metric","3"
"C58,C59","2.2u","Capacitor_SMD:C_0603_1608Metric","2"
"C61-C64","18p","Capacitor_SMD:C_0402_1005Metric","4"
"C74,C75","20F 3.0V","Capacitor_THT:CP_Radial_D12.5mm_P5.00mm","2"
"C86,C92","4.7n","Capacitor_SMD:C_0603_1608Metric","2"
"C95,C97,C103,C116,C181,C222,C224","10n","Capacitor_SMD:C_0603_1608Metric","7"
"C117,C119,C185","1n","Capacitor_SMD:C_0603_1608Metric","3"
"C123,C198,C202","470n","Capacitor_SMD:C_0603_1608Metric","3"
"C132,C134,C136,C138,C140,C142,C147,C149,C154,C156,C158,C160,C162,C164,C166,C168,C170,C172,C174,C176,C178,C187","100n","Capacitor_SMD:C_1206_3216Metric","22"
"C197,C201","68n","Capacitor_SMD:C_0603_1608Metric","2"
"C226,C229","2.2u","Capacitor_SMD:C_0805_2012Metric","2"
"C241,C243,C245,C249,C251,C253","4.7u","Capacitor_SMD:C_0805_2012Metric","6"
"C257,C258","22p","Capacitor_SMD:C_0402_1005Metric","2"
"D1","SMDJ36CA","Diode_SMD:D_SMC","1"
"D2,D68,D69,D74,D76,D78,D80,D82,D84,D86,D88,D90,D92,D94,D96,D98,D100,D102,D123,D126","SMBJ33CA","Diode_SMD:D_SMB","20"
"D3,D4","BAS70","Package_TO_SOT_SMD:SOT-23","2"
"D5","SMBJ5.0A","Diode_SMD:D_SMB","1"
"D6,D9,D103-D119","green","LED_SMD:LED_0805_2012Metric","19"
"D7,D8,D121","BAT54C","Package_TO_SOT_SMD:SOT-23","3"
"D10,D124","red","LED_SMD:LED_0805_2012Metric","2"
"D11","SS34","Diode_SMD:D_SMA","1"
"D12,D13","NUP2105L","Package_TO_SOT_SMD:SOT-23","2"
"D14,D15,D64,D73,D75,D77,D79,D81,D83,D85,D87,D89,D91,D93,D95,D97,D99,D101,D120,D122","SS110","Diode_SMD:D_SMA","20"
"D16","SM712","Package_TO_SOT_SMD:SOT-23","1"
"D17,D18","RClamp0524P","genctl:RClamp0524P_SLP2510P8","2"
"D19-D21","USBLC6-2SC6","Package_TO_SOT_SMD:SOT-23-6","3"
"D22","SS36","Diode_SMD:D_SMA","1"
"D23","LM4040A25","Package_TO_SOT_SMD:SOT-23","1"
"D24,D27,D30,D33,D36,D39,D42,D44,D46-D58,D66","SMAJ36CA","Diode_SMD:D_SMA","22"
"D25,D28,D31,D34,D37,D40,D127","1N4148W","Diode_SMD:D_SOD-123","7"
"D26,D29,D32,D35,D38,D41,D43,D45,D60,D62","BAV99","Package_TO_SOT_SMD:SOT-23","10"
"D59,D61","SMBJ58CA","Diode_SMD:D_SMB","2"
"D63","SMBJ36CA","Diode_SMD:D_SMB","1"
"D65,D67,D125","BAT54S","Package_TO_SOT_SMD:SOT-23","3"
"D70,D72","SK1010C","Diode_SMD:D_SMC","2"
"D71","SMDJ24A","Diode_SMD:D_SMC","1"
"F1","10A ATO (3557-2 clips)","genctl:Keystone_3557-2_ATO_clips","1"
"FB1","600R@100MHz","Inductor_SMD:L_0603_1608Metric","1"
"H1-H4","MountingHole_Pad","MountingHole:MountingHole_3.2mm_M3_Pad","4"
"J1","PC 5/4-GF-7,62 (battery in)","genctl:PhoenixContact_PC5_4-GF-7.62_1720819","1"
"J2","SWD","genctl:FTSH-105-01_SWD","1"
"J3","Header B (MCU spare)","genctl:PZ254-2-05-S_2x05_SMD","1"
"J4","Fan header (SM04B)","Connector_JST:JST_SH_SM04B-SRSS-TB_1x04-1MP_P1.00mm_Horizontal","1"
"J5","Header A (CM5 I2C/SPI)","genctl:PZ254-2-05-S_2x05_SMD","1"
"J6","CAN1 (PC 5/4)","genctl:WJ15EDGRC-3.81-4P","1"
"J7","Expansion bus (PC 5/6)","genctl:WJ15EDGRC-3.81-6P","1"
"J8","Router 12V (3.81/2)","genctl:WJ15EDGRC-3.81-2P","1"
"J9","RS-485 (PC 5/3)","genctl:WJ15EDGRC-3.81-3P","1"
"J10","HR963380AE","genctl:HR963380AE_RJ45","1"
"J11","USB-C service","genctl:USB_C_Receptacle_HRO_TYPE-C-31-D-06B_Vertical","1"
"J12","Internal USB0 touch (SM04B)","Connector_JST:JST_SH_SM04B-SRSS-TB_1x04-1MP_P1.00mm_Horizontal","1"
"J13","Internal USB1 spare (SM04B)","Connector_JST:JST_SH_SM04B-SRSS-TB_1x04-1MP_P1.00mm_Horizontal","1"
"J14","LVDS FPC 40p 0.5mm","genctl:FPC_40P_0.5_05A20L40P","1"
"J15","Touch FPC 10p 0.5mm","genctl:FPC_10P_0.5_05B20L10P","1"
"J16","Backlight (JST SM02B-BHSS)","genctl:SM02B-BHSS-1-TB","1"
"J17","J1A analog in (PC 5/6)","genctl:KF2EDGRM-5.08-6P","1"
"J18","J1B COM/MPU (PC 5/6)","genctl:KF2EDGRM-5.08-6P","1"
"J19","J2A DI1-6","genctl:KF2EDGRM-5.08-6P","1"
"J20","J2B DI7-12","genctl:KF2EDGRM-5.08-6P","1"
"J21","J3A E-stop/D+/VBAT/bias","genctl:KF2EDGRM-5.08-6P","1"
"J22","J3B","genctl:KF2EDGRM-5.08-6P","1"
"J23","J4 E-stop/fuel/crank (PC 5/4-7.62)","genctl:PhoenixContact_PC5_4-GF-7.62_1720819","1"
"J24","J5A outputs","genctl:KF2EDGRM-5.08-6P","1"
"J25","J5B returns","genctl:KF2EDGRM-5.08-6P","1"
"J26","J6A AUX1-6","genctl:KF2EDGRM-5.08-6P","1"
"J27","J6B AUX7-10 + returns","genctl:KF2EDGRM-5.08-6P","1"
"J28","J7 GEN voltage (L1 L2 L3 N)","genctl:PhoenixContact_PC5_4-GF-7.62_1720819","1"
"J29","J8 BUS voltage (L1 L2 L3 N)","genctl:PhoenixContact_PC5_4-GF-7.62_1720819","1"
"J30","J9 CT secondaries (5A)","genctl:KF2EDGRM-5.08-8P","1"
"JP1","JP1 CM5->MCU SWD (opt)","Connector_PinHeader_2.54mm:PinHeader_2x04_P2.54mm_Vertical","1"
"L1","4.7u","genctl:L_SPM10065","1"
"L2","3.3u","genctl:L_MWSA1004S","1"
"L3","2.2u","genctl:L_MWSA0503S","1"
"L4","33u","genctl:L_SWPA6045S","1"
"L5","1u","genctl:L_FNR5020S","1"
"L6,L7","ACT45B-510-2P","genctl:ACT45B_CMC","2"
"L8","10u","genctl:L_SWPA6045S","1"
"Q1-Q6,Q45-Q48","BSC070N10NS5","Package_TO_SOT_SMD:TDSON-8-1","10"
"Q7-Q11,Q14,Q18,Q22,Q26,Q30,Q34,Q37,Q40,Q43,Q44,Q49-Q67,Q69","MMBT3904","Package_TO_SOT_SMD:SOT-23","35"
"Q12,Q16,Q20,Q24,Q28,Q32","MMBT3906","Package_TO_SOT_SMD:SOT-23","6"
"Q13,Q17,Q21,Q25,Q29,Q33","BSS84","Package_TO_SOT_SMD:SOT-23","6"
"Q15,Q19,Q23,Q27,Q31,Q35,Q38,Q41","DMN6075S","Package_TO_SOT_SMD:SOT-23","8"
"Q36,Q39,Q42","SI2309CDS","Package_TO_SOT_SMD:SOT-23","3"
"Q68","AO3401A","Package_TO_SOT_SMD:SOT-23","1"
"R1","210k","Resistor_SMD:R_0603_1608Metric","1"
"R2","49.9k","Resistor_SMD:R_0603_1608Metric","1"
"R10,R17,R24,R31,R42,R44,R45,R48,R49,R63,R65,R67,R69,R70,R72,R74,R78,R79,R83,R101,R113,R117,R118,R124,R127,R128,R132,R135,R143,R146,R154,R157,R165,R168,R176,R179,R187,R190,R202,R207,R257,R263,R267,R269-R272,R274,R351,R354,R357,R360,R363,R366,R369,R372,R375,R378,R381,R384,R387,R390,R393,R396,R399,R401,R402,R412,R420,R421,R528","10k","Resistor_SMD:R_0603_1608Metric","71"
"R4,R11,R19,R26,R28,R32,R43,R64,R66,R68,R71,R73,R81,R97,R110,R112,R114-R116,R121,R133,R134,R136,R138,R139,R144,R145,R147,R149,R150,R155,R156,R158,R160,R161,R166,R167,R169,R171,R172,R177,R178,R180,R182,R183,R188,R189,R191,R193,R194,R196,R198,R200,R201,R203-R206,R208,R209,R261,R262,R264,R266,R268,R273,R275-R292,R298,R350,R353,R356,R359,R362,R365,R368,R371,R374,R377,R380,R383,R386,R389,R392,R395,R398,R403,R405,R406,R411,R527,R530","100k","Resistor_SMD:R_0603_1608Metric","108"
"R5,R212,R215,R218,R221,R224,R227,R230,R233,R236,R239,R242,R245,R248,R250,R252","33k","Resistor_SMD:R_0603_1608Metric","16"
"R6","93.1k","Resistor_SMD:R_0603_1608Metric","1"
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

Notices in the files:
mechanical/pcb_v4/genctl_v4_handrouted.kicad_pcb:
genctl rev H  layout v4  CERN-OHL-S-2.0
